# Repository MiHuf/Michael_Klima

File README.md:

[Zu bearbeiten mit keenwrite.bin oder retext,  File README.md, Version 2025-03-30]: #
# Michael_Klima

Michaels Raumklima-Monitor. Inspiriert durch den Artikel
"IKEA Vindiktning hacken", siehe Make 5/2021, Seite 14 ff und hier: <https://techtest.org/anleitung-wlan-feinstaub-und-temperatur-sensor-ikea-vindriktning-hack/>

Der Code ist vorbereitet für den Anschluß weiterer Sensoren.
Im Original: VINDRIKTNING Ikea Luftgüte Sensor -> AdafruitIO

Mai 2022: Absolute (aber ungenaue) Helligkeitsmessung mit einem LDR Photowiderstand. Parameter müssen in der jeweiligen Zugangsdaten-Datei xxx.h angepasst werden. Siehe LDR-Photometer.pdf.

Sept. 2023: Luftdruck-Sensor BME280 eingebaut, CO2-Sensor SCD-30 vorbereitet.

Okt. 2024: Doku ergänzt.

Nov. 2024: MQTT funktioniert, Doku aktualisiert

Dez. 2024: MQTT jetzt sowohl mit Port 1883 als auch mit Port 8883 (TLS)

Mrz. 2025: Erweitert auf beliebig viele (zur Zeit 10) DS18x20 Sensoren

## Konfiguration und Installation

  1. Den Projekt-Ordner "Michael_Klima" von github.com/MiHuf/ klonen.

  2. Der Mircocontroller "Wemos D1 Mini ESP8266" wird programmiert mit der Arduino IDE <https://www.heise.de/ct/artikel/Arduino-IDE-installieren-und-fit-machen-fuer-ESP8266-und-ESP32-4130814.html>. Die Sprache ist im Wesentlichen C++.  
Vorher müssen noch einige Dateien angepasst werden:

  3. ***Datei "Michael_Klima.h", Zeile 51:***

      #include "privat.h"   
Die Datei "privat.h" enthält persönliche Zugangsdaten. Am besten nimmt man die als Gerüst und kopiert sie in eine neue Datei, z.B. "_mein_privat.h". Alle Dateien mit einem Unterstrich am Anfang des Namens werden von git nicht im öffentlichen Repository gespeichert.  
Anschließend muss die Zeile 56 entsprechend angepasst werden:  
  #include "_mein_privat.h"  

  4. ***Datei "_mein_privat.h":*** 
  
      4.1. In den Zeilen 23 bis 52 sind die aktuell vorhandenden Sensoren definiert, die Zeilen können gelöscht oder umgeordnet werden. 
 
      4.2. In die Sektion "\***** My Settings" kommen dann die privaten Zugangsdaten:  
   #define WIFI_SSID "xxx"  
   #define WIFI_PASS "yyy"  
Das sind die Zugangsdaten zum lokalen WLAN des Routers und ggf. zum Internet.

     4.3. Falls erforderlich, Daten für den MQTT Broker konfigurieren: TOPIC, MQTT_BROKER, MQTT_PORT,  MQTT_USER, MQTT_PASS, ...  
     Achtung: Falls "MQTT_PORT 8883" für TLS gesetzt wird, muss zusätzlich eine Zeile  
   #define MQTT_TLS  
eingefügt werden. Für "MQTT_PORT 1883" muss diese Zeile auskommentert werden.  

      4.4 Der Wemos D1 Mini ESP8266 in dem Modul spannt eigenes WLAN auf, das wird konfiguriert in den Zeilen  
   #define APSSID "zzz"  
   #define OPEN_WIFI  
Das sind die Zugangsdaten zum internen WLAN des ESP8266 (ohne Passwort).

5. ***Anschließend mit der Arduino IDE kompiliern,*** das Modul mit einem Mirco-USB Kabel an den PC anschließen und den Binär-Code auf den D1 Mini hochladen.

    Der ESP8266 konfiguriert sich dann und startet das Programm. Das kann bis zu 2 Minuten dauern, am Ende wird die eingebaute LED fünf mal blinken.

6. ***Für den nächsten Schritt gibt es 2 Möglichkeiten:***

    6.1 Mit einem anderen PC / Touchpad / Handy das WLAN Netzwerk scannen und mit der in Abschnitt 4.2 definierten APSSID (z.B. "zzz") verbinden.

      Dann mit einem Browser (Firefox, Chrome) die Seite `http://192.168.4.1` öffnen. Dann sollte sich eine Seite mit wichtigen Informationen über das Netzwerk öffnen. Merke dir aus der Zeile "External WLAN SSID" den Wert von "IP address" und aus der folgenden Zeile den Wert von "Hostname on Router".

      Falls in der Zeile "External WLAN SSID" keine IP-Adresse angezeigt wird, hat die Verbindung zum WLAN des Routers nicht geklappt. Überprüfe die Zugangsdaten und wiederhole ab Abschnitt 4.2.

    6.2 Gehe auf die Administrations-Seite des Routers, lass dir im Abschnitt "WLAN > Funknetz" die verbundenen Geräte anzeigen. Der ESP8266 sollte unter dem Namen Raumklima-XXX sichtbar sein, wobei XXX die letzten 6 Hex-Ziffern der MAC Addresse ist. Merke dir die zughörige IP-Adresse.

7. ***Geschafft!***
  Ab jetzt sollte der Raumklima Monitor von überall im LAN mit einem Browser sichtbar sein, entweder über die obige IP-Adresse oder über die URL `"http://raumklima-xxx"`.

8. ***Optional:***
  Um einen Zugriff von außen übers Internet einzurichten, muss man im Router einen DDNS-Client installieren und konfigurieren und ferner für raumklima-xxx eine Port-Weiterleitung zur <IP-Adresse des Moduls>:80 erstellen.

## Life Demo

Klicke hier: <http://hufschmidt.ddns.krude.de:8086/> oder <http://hufschmidt.ddns.krude.de:8087/>

## Setup März 2022:

Und hier die Adapter-Platine (35mm x 42mm):

## Quellen für den Arduino Code und für MQTT  Broker
|Was     |URL|
|--------|------------------------------------------------------------------------|
|ESP8266:|<https://github.com/esp8266/Arduino/tree/master/libraries/ESP8266WiFi/>|
|Time-Server:|<https://werner.rothschopf.net/201802_arduino_esp8266_ntp.htm>|
|OneWire:|<https://github.com/PaulStoffregen/OneWire/blob/master/OneWire.h>|
|        |<https://www.arduino.cc/reference/en/libraries/onewire/>|
|DS18B20:|<https://github.com/milesburton/Arduino-Temperature-Control-Library/blob/master/DallasTemperature.h>|
|DHT11:  |<https://cdn-learn.adafruit.com/downloads/pdf/dht.pdf>|
|        |<https://github.com/adafruit/DHT-sensor-library>|
|BME280: |<https://www.az-delivery.de/products/gy-bme280>|
|SCD-30: |<https://www.adafruit.com/product/4867>|
|        |<https://learn.adafruit.com/adafruit-scd30/arduino>|
|MQTT Client Lib|<https://github.com/knolleary/pubsubclient>|
|MQTT Broker Mosquitto:|<http://www.steves-internet-guide.com/install-mosquitto-linux/>|
|InfluxDB:|<https://www.ionos.de/digitalguide/hosting/hosting-technik/was-ist-influxdb/>|
|Grafana: |<https://grafana.com/>|
|MQTT Client Software zum Testen|<http://mqtt-explorer.com/>|
|MQTT Broker, Übersicht|<https://mntolia.com/10-free-public-private-mqtt-brokers-for-testing-prototyping/>|
|MQTT Broker HiveMQ:| <https://www.hivemq.com/>|
|MQTT Broker Cedalo / Pro Mosquitto| <https://test.mosquitto.org/>|
|MQTT Broker flespi|<https://flespi.com/>|
|MQTT Broker sensatio:|<https://www.sensatio.io/>|

---

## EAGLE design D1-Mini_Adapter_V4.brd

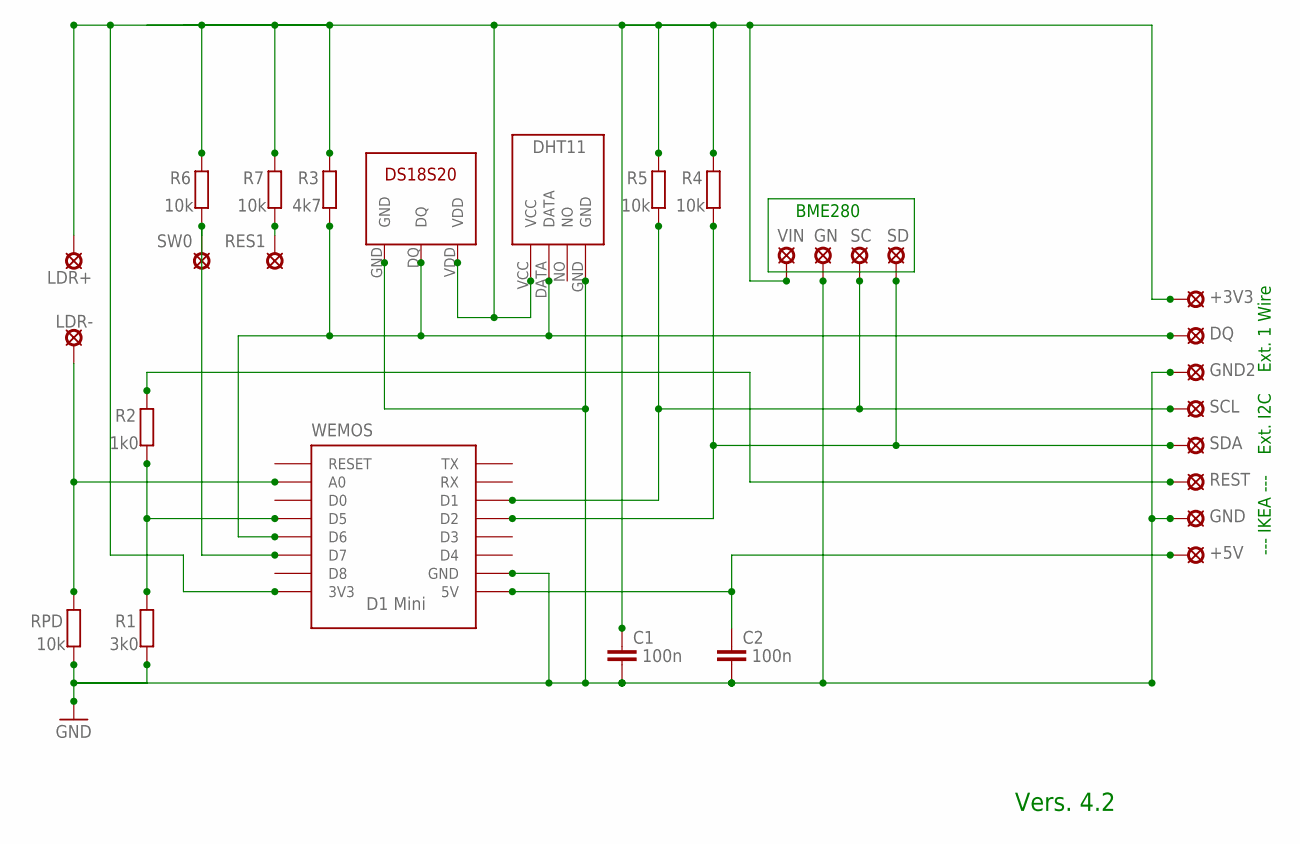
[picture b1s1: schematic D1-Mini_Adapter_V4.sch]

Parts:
+3V3, +5V: SE13
C1, C2: 100n; C025_050-045X075
DQ: SE13
DS1820: DS18S20; DS18S20-PACKAGE
GN: SE13
GND, GND2: SE13
LDR+: SE13
LDR-: SE13
R1: 3k0; 0207/10
R2: 1k0; 0207/10
R3: 4k7; 0207/10
R4, R5, R6, R7: 10k; 0207/10
RES1: SE13
REST: SE13
RPD: 10k; 0207/10
SC: SE13
SCL: SE13
SD: SE13
SDA: SE13
SW0: SE13
U$1: DHT11-PION.
VIN: LSP13
WEMOS: D1 Mini; WEMOS-D1-MINI

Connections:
3V3: +3V3.MP, C1.1, DS1820.VDD, LDR+.MP, R3.2, R4.2, R5.2, R6.2, R7.2, U$1.VCC, VIN.MP, WEMOS.3V3
+5V: +5V.MP, C2.1, WEMOS.5V
D5: R1.2, R2.1, WEMOS.D5
DQ: DQ.MP, DS1820.DQ, R3.1, U$1.DATA, WEMOS.D6
GND: C1.2, C2.2, DS1820.GND, GN.MP, GND.MP, GND2.MP, R1.1, RPD.1, U$1.GND, WEMOS.GND
LDR: LDR-.MP, RPD.2, WEMOS.A0
RES1: R7.1, RES1.MP
REST: R2.2, REST.MP
SCL: R5.1, SC.MP, SCL.MP, WEMOS.D1
SDA: R4.1, SD.MP, SDA.MP, WEMOS.D2
SW0: R6.1, SW0.MP, WEMOS.D7

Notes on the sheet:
--- IKEA ---
Ext. I2C
Ext. 1 Wire
Vers. 4.2
BME280

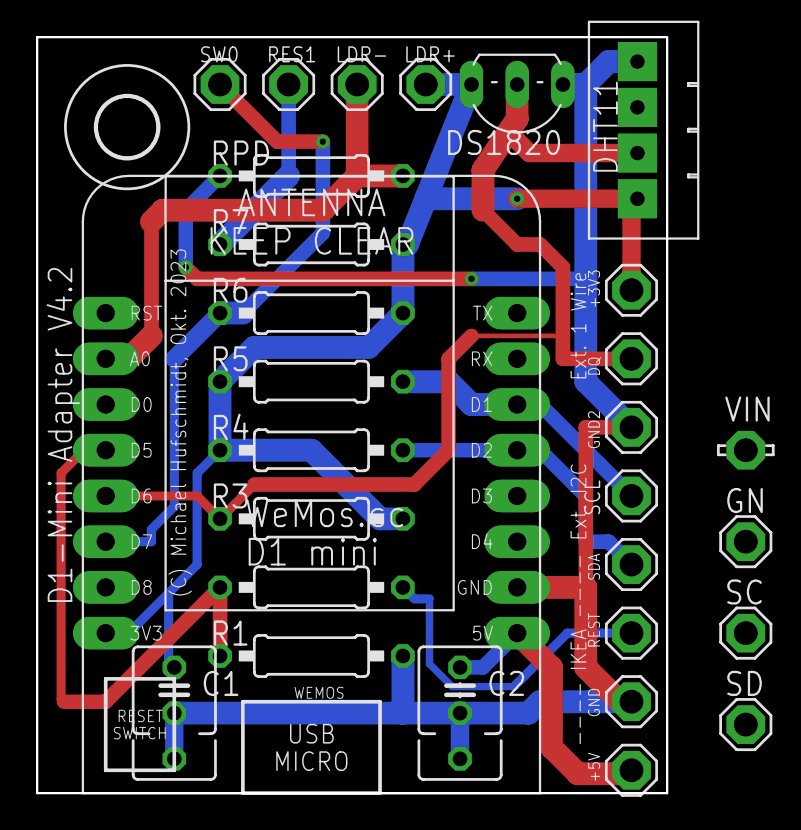
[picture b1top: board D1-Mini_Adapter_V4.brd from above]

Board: 2 copper layers, 35.0 x 42.0 mm, 30 parts (0 on the bottom side), 11 nets.

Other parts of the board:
U$2: 3,3

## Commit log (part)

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2022-04-29 Initial Version
2022-04-29 now using the internal web-server
2022-04-29 file structure modified
2022-04-29 separate file for sensor definition
2022-04-29 MQTT client now working
2022-04-30 some documentation
2022-04-30 mehr Dokumentation, mit Bildern
2022-04-30 Kosmetik
2022-05-01 Doku weiter ergänzt
2022-05-03 Abfrage TEST_MODE von Michael_Klima.ino nach Michael_Sensoren.h
2022-05-03 neue Funktion getRandom() verwendet
2022-05-04 Fixed sections PRIVAT_H & IM_INSTITUT_H
2022-05-04 fixed section IM_INSTITUT
2022-05-04 Bugfix Zeile 15
2022-05-04 ntp Timestanp hinzugefügt
2022-05-05 MY_NTP_SERVER verschoben von Michael_Klima.ino in die User-Files
2022-05-06 #define APPSK moved from Hichael_Klima.h to user files, new option OPEN_WIFI
2022-05-07 Vorbereitet für einen Analog-Sensor
2022-05-07 Michael_Sensoren.h deleted, Sensor-Definitions moved to Michael_Klima.h and the individual user files
2022-05-07 Doku angepasst
2022-05-09 HAS_INTERNET set
2022-05-10 fixed unclear line comment for OPEN_WIFI
2022-05-10 moved processInterval and refreshInterval from Michael_Klima.ino to Michael_Klima.h
2022-05-23 Doku für LDR Photometrie
2022-05-24 kleine Ergänzung, danke an Michael Heinz
2022-05-31 Bugfix in den Plots auf Seite 2, Wertetabelle hinzugefügt
2022-05-31 LDR Photometrie hinzugefügt
2022-06-08 all .a - files beginning with underscores considered as private
2022-06-12 adapted for LDR photoresistor
2022-06-14 now accepting arbitrary order of the sensor array
2022-06-15 added comment
2022-06-17 bits and bobs
2022-06-19 compiler falges modified
2022-06-20 compiler flags modified, typo corrected
2022-06-22 fixed logical bug in getLDR()
2022-06-22 set LDR type
2022-06-22 LF -> CR LF
2022-12-13 PCB Version 3.1
2022-12-15 Silkscreen improved
2022-12-15 Schematics aktualisiert
2022-12-15 Filename schematic fixed
2023-04-26 #define DHTTYPE xxx moved to individual header files
2023-05-17 Doku improved
2023-05-18 additional Comments
2023-06-25 Added info about MQTT User
2023-06-28 Kosemtik
2023-06-28 ignore Arduio Libraries
2023-07-09 Eagle files added
2023-07-11 Schaltplan übersichtlicher
2023-09-11 Added Sensores BME280 and SCD-30
2023-09-11 Dokumantation
2023-09-12 preparing more sensors, documentation
2023-09-14 minor improvements in sensor detection
2023-09-14 default is privat.h
2023-09-15 MQTT activated
2023-09-18 Doku adapted and extented
2023-09-19 modified MQTT stuff
2023-09-20 Minor modifications, incl. documentation
2023-09-21 calculation for Rpd = 10 kOhm
2023-09-21 Doku for Rpd = 10 kOhm
2023-09-21 MQTT stuff, still not connecting
2023-09-22 Doku: added InfluxDB and Grafana
2023-09-23 Bugfix README
2023-09-24 MQTT reconnect(): new param maxTries
2023-09-28 Fixed bad HTML Code in buildHtml()
2023-09-28 added functionality MQTT_IF_LOW, improved buildHtml()
2023-09-29 New PCS Version 4.1
2023-09-29 Board V4.1
2023-09-29 Documentation adapted for PCB Version 4.1
2023-10-02 renamed some include files
2023-10-05 PCB and schema Version 4.2
2023-10-25 added option for _test1.h
2024-09-11 Kleinere Änderungen
2024-09-26 added MY_SERVERNAME
2024-09-26 #include korrigiert
2024-10-03 added servernam_s to HTML-Info
2024-10-03 fixed comment
2024-10-06 Abschnitt Konfiguration und Installation ausführlicher
2024-10-07 Typos eliminiert, formatiert
2024-10-07 formatiert
2024-10-09 reformatted using keenwrite.bin
2024-10-09 again reformatted using keenwrite.bin
2024-10-24 espClient now an instance of WiFiClient instead of WiFiClientSecure, MQTT connectOK now true
2024-10-24 minor improvements
2024-10-28 MQTT publish works most of the time
2024-10-30 added some files and dirs
2024-11-01 modified mqtt_client_id calculation, HTML Output
2024-11-01 improved make_html()
2024-11-02 improved MQTT publish()
2024-11-04 MQTT publish now with timestamp before sensor data
2024-11-07 added functions getSwitchNum_xxx() with numerical output
2024-11-11 new Option to set individual timing
2024-11-11 Doku aktualisiert
2024-11-11 Bugfix INDIVIDUAL_TIMING
2024-11-11 modified blinking frequency
2024-11-12 temp files ignored
2024-11-13 cleaned
2024-12-03 Prepared for SSL using BearSSL
2024-12-05 Now also working with MQTT and TLS (Port 8883)
2024-12-05 Now working with both Ports 1883 and 8883
2024-12-08 Switch between Ports 1883 and 8883 now with compiler directive MQTT_TLS
2024-12-09 doc improved
2025-03-29 Erweitert auf beliebig viele (zur Zeit 5) DS18x20 Sensoren
2025-03-30 Kosmetik & max. Anzahl DS-Sensoren jetzt 10
2025-04-01 reduced code-size with more elegant programming
2025-04-04 minor bug
2025-06-19 modularized setup_sensors()
2026-05-27 added IDE info
2026-06-01 mostly Documentation
2026-06-02 Comments improved
2026-06-13 new IDE Version
2026-06-14 New IDE
